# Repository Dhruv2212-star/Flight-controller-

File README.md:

# ASTRA FLIGHT CONTROLLER
The Astra Flight Controller is a custom-designed flight control board developed for multirotor unmanned aerial vehicles (UAVs). It is built around the STM32F411CEU6 microcontroller and the ICM-42688-P six-axis Inertial Measurement Unit (IMU), providing a compact, high-performance platform capable of running modern flight control firmware such as Betaflight, INAV, or customdeveloped firmware
1. **Main Features**
* STM32F411CEU6 ARM Cortex-M4 Microcontroller  
* ICM-42688-P 6-axis IMU  
* MP2359DJ High-Efficiency 5 V Buck Converter  
* AP2112K 3.3 V Low-Dropout Voltage Regulator  
* USB Type-C Interface  
* SWD Programming Header  
* XT30 Battery Input  
* Active Buzzer Driver Circuit  
* Status LED  
* External UART Expansion  
* Dedicated SPI Interface for the IMU  
* Compact PCB designed within a 100 mm × 100 mm manufacturing limit
  2. **Hardware Architecture**  
* Power Management  
* Processing Unit  
* Sensor System  
* Communication Interfaces  
* User Interface  
* Programming & Debugging  
* External Connections  
 3. **Hardware Modules Power Management**
Responsible for converting battery voltage into stable regulated voltages used by the board.
Major Components:
* XT30 Battery Connector  
* Resettable Fuse  
* MP2359DJ Buck Converter  
* AP2112K 3.3V Regulator Filtering Capacitors Outputs:  
 +5V Rail  
 +3.3V Rail  
4. **Processing Module**
The processing module is the "brain" of the flight controller. Main Component: STM32F411CEU6.
Responsibilities:  
* Reads sensor data  
* Executes flight control algorithms  
* Controls motors  
* Handles USB communication  
* Processes receiver input  
* Generates PWM/DShot signals    
* Controls LEDs and buzzer  
 5. **Sensor Module** 
The sensor subsystem provides real-time motion data.  
Main Sensor: ICM-42688-P.  
 
Measurements: 3-axis Accelerometer, 3-axis Gyroscope. Communication: SPI Interface.  
The IMU continuously measures angular velocity and acceleration  
**Power-Up Sequence**
*When battery power is applied, the following sequence occurs:*
Step 1: Battery voltage enters through the XT30 connector.  
Step 2: The resettable fuse protects the board from excessive current.  
Step 3: The MP2359DJ converts battery voltage into a regulated +5V supply.  
Step 4: The AP2112K converts +5V into +3.3V.  
Step 5: The STM32F411CEU6 receives stable power.   
Step 6: The crystal oscillator starts generating the system clock.  
Step 7: The microcontroller boots from Flash memory.  
Step 8: The SPI interface initializes the ICM-42688-P.  
Step 9: Sensors begin transmitting motion data.  
Step 10: the flight controller enters normal operating mode 

------------------------------------------------------------------------------------------------------------------------------------------

**Clock Generation**
The STM32F411CEU6 uses an external crystal oscillator for accurate timing. The external crystal provides stable CPU clock, accurate USB timing, reliable SPI communication, and consistent sensor sampling. Proper placement of the crystal and its load capacitors is essential for reliable operation.  

**power system**
Why Two Regulators?  
Using a single linear regulator directly from the battery would result in excessive heat generation, especially at higher input voltages. Instead, the Astra Flight Controller uses a two-stage regulation    
approach:  
* MP2359DJ Buck Converter — efficiently reduces battery voltage to 5 V.  
* AP2112K LDO — produces a clean and stable 3.3 V output with minimal electrical  
noise. This combination provides both efficiency and stable operation.  

**STM32F411CEU6 Microcontroller**
The STM32F411CEU6 is the primary processing unit of the Astra Flight Controller. It executes the flight control firmware, processes sensor data, generates motor outputs, and manages all communication interfaces.
Role-   
The STM32 reads IMU data through SPI, executes flight control algorithms, generates ESC outputs, monitors battery voltage, controls the LED and buzzer, manages USB communication, and supports firmware programming through SWD.  

## ICM-42688-P Inertial Measurement Unit (IMU)  
 *Introduction*  
The ICM-42688-P is the primary motion sensing device used in the Astra Flight Controller. It integrates a 3-axis accelerometer and a 3-axis gyroscope in a compact LGA package. The sensor continuously measures aircraft motion and sends this data to the STM32F411CEU6 through the SPI interface for attitude estimation and flight stabilization.    
**Why the ICM-42688-P was Selected?**  
The sensor was selected because of its excellent gyroscope noise performance, high sampling rate, low latency, low power consumption, compact size, and broad support in modern flight-control firmware such as Betaflight and INAV.  
Main Specifications:-  
* Device- ICM-42688-P  
* Sensor Type- 6-Axis IMU  
* Accelerometer- 3-Axis MEMS  
* Gyroscope- 3-Axis MEMS  
* Operating Voltage- 1.71–3.6 V  
* Communication- SPI / I²C  
* Max SPI Clock Up to 24 MHz  
* Operating Temp −40°C to +85°C    
**Working Principle**  
The accelerometer measures linear acceleration along the X, Y, and Z axes, while the gyroscope  
measures angular velocity about the same axes. Together they provide six degrees of freedom (6-DoF), allowing the firmware to estimate   the aircraft's orientation using sensor-fusion algorithms.  
**Hardware Integration**  
The IMU operates from the regulated 3.3 V rail. VDD and VDDIO are connected to 3.3 V, while the GND pins connect directly to the ground plane. Local decoupling capacitors are placed close to the power pins to reduce supply noise and improve stability.    
**SPI Communication**  
Communication with the STM32F411CEU6 takes place over SPI using SCK, MOSI, MISO, and CS. SPI was selected instead of I²C because it offers higher bandwidth, lower latency, and improved reliability in electrically noisy environments.  
**Interrupt Output**
The interrupt pin notifies the STM32 whenever new sensor data is available, reducing processor workload and improving the timing of the flight-control loop.  

The IMU continuously measures aircraft motion, sends accelerometer and gyroscope data to the STM32 through SPI, and the firmware processes this information to estimate attitude and generate motor control outputs.  

## USB Type-C Interface

*Introduction*  
The USB Type-C interface serves as one of the primary communication and power interfaces of the Astra Flight Controller. It provides firmware flashing, debugging, configuration, diagnostics and  
development power.  
USB Type-C offers reversible insertion, improved durability, better current capability and long-term compatibility. The design uses the USB 2.0 Full-Speed interface connected directly to the STM32F411CEU6.   

**Purpose**
Firmware upload, configuration using Betaflight/INAV/STM32CubeProgrammer, debugging through serial communication, and powering the board during development without a LiPo battery  
**Advantages**  
Reversible connector, stronger mechanical retention, higher current capability and modern industrystandard compatibility.  
**USB Connector**
| Pin | Function |  
| VBUS | +5V |  
| GND | Ground |  
| D+ | USB Data Positive |  
| D- | USB Data Negative |  
| CC1 | Configuration Channel 1 |  
| CC2 | Configuration Channel 2 |  
| Shield | Connector Shield |  

**Data Communication**
USB Full-Speed uses the D+ and D− differential pair. Route them together with matched lengths, minimal vias, constant spacing, no sharp bends and a continuous ground plane. The STM32F411CEU6 supports USB 2.0 Full-Speed (12 Mbps), sufficient for firmware updates and configuration  
##  XT30 Battery Connector
The XT30 connector is the primary battery input. Battery voltage enters the board through the XT30 connector, passes through the resettable fuse and protection circuitry, and then feeds the MP2359DJ buck converter. Wide copper traces are used to carry battery current and minimise voltage drop.  
## ESC Connections
Motor control signals generated by the STM32 are routed to the ESC outputs. These connections carry logiclevel control signals only; motor power is supplied separately by the battery through the ESCs.   
#  Indicators and User Interface
**Overview**  
The Astra Flight Controller includes a status LED, a TL3342 push button and an active buzzer. These devices provide visual, audible and manual interaction during development, testing and flight operation.  
**Status LED**
The STM32 controls the LED to indicate power, boot status, firmware activity, calibration, arming state and error conditions.  
**Push Button**
The TL3342 tactile switch can be used for boot mode selection, firmware recovery, calibration and user-defined functions through a GPIO input.  
**Active Buzzer**
The active buzzer provides audible feedback including startup, arming, low-battery and fault indications. It requires only an on/off control signal from the STM32.  
## Component Placement Strategy
1. Microcontroller Placement  
The STM32F411CEU6 is positioned near the center of the PCB. This location minimizes the average distance between the MCU and all connected peripherals, resulting in shorter SPI traces, shorter USB connections, reduced propagation delay, easier routing, and improved signal integrity. The exposed thermal pad beneath the MCU is connected directly to the ground plane for both thermal dissipation and electrical grounding.  
2. IMU Placement  
The ICM-42688-P is the most sensitive component on the board. To maximize Measurement accuracy, it is placed close to the center of the PCB, kept away from the MP2359DJ buck converter and inductor, and highcurrent traces are not routed beneath the sensor. A continuous ground plane is maintained underneath the device, and the sensor orientation matches the coordinate system  
expected by the firmware.  
Proper placement reduces electrical interference and vibration-induced measurement errors  
**Power Section Placement**
The power conversion circuitry is grouped together near the battery input. This includes:  
* XT30 connector.  
* Resettable fuse.  
* Protection diode.  
* MP2359DJ buck converter.  
* 4.7 µH Bourns SRP5030TA-4R7M inductor.  
* Input and output capacitors.  
* AP2112K voltage regulator.  
## Power Supply Design
The Astra Flight Controller is designed to operate directly from a 2S to 6S Lithium Polymer (LiPo) battery, meaning the input voltage can vary from approximately 7.4 V to 25.2 V. To achieve stable regulation, the Astra Flight Controller uses a two-stage power architecture: the MP2359DJ synchronous buck converter generates a regulated 5 V supply from the battery, and the AP2112K Low Dropout (LDO) regulator generates a clean 3.3 V supply from the 5 V raiL  

 Power Flow
2S–6S LiPo Battery  
|  
XT30 Battery Connector  
|  
Resettable Fuse (F1)  
|  
TVS / Reverse Protection  
|  
MP2359DJ Buck Converter — +5 V Rail  
|  
AP2112K LDO Regulator — +3.3 V Rail  
|  
STM32F411 
|  
ICM-42688  
##  Resettable Fuse (F1)
Immediately after the XT30 connector, the input passes through a resettable polyfuse (PTC), which protects the PCB from excessive current caused by short circuits, incorrect wiring, component failures, or assembly mistakes. Unlike a traditional fuse, the polyfuse automatically resets after the fault is removed and the device cools down.  

## MP2359DJ Buck Converter
1. Why a Buck Converter?
A linear regulator would dissipate the voltage difference between the battery and the output as heat. Converting 25.2 V from a fully charged 6S battery directly to 5 V using a linear regulator would result in excessive power loss and unacceptable temperatures. A switching buck converter solves this problem by rapidly switching the input voltage through an inductor and filtering the output,
achieving efficiencies typically above 85–90%.  
2. MP2359DJ Features  
* Wide input voltage range.  
* High conversion efficiency.  
* Integrated MOSFETs.  
* Compact package.  
* High switching frequency.  
* Internal protection features.  
* Minimal external components.  
3. Operating Principle  
The MP2359DJ is a synchronous step-down (buck) switching regulator. Its operation consists of four basic stages: the internal MOSFET switches ON allowing current to flow into the inductor; energy is stored in the magnetic field of the inductor; the MOSFET switches OFF; and the inductor releases stored energy through the output filter, maintaining a continuous output voltage. This cycle repeats
hundreds of thousands of times per second.
External Components-- 
● Input capacitor.
● Output capacitor.
● Bootstrap capacitor.
● Schottky protection diode (where applicable).
● Feedback resistor network.
● 4.7 µH power inductor

 # Manufacturing 
The PCB is designed to be compatible with standard manufacturing services such as JLCPCB while
remaining within the 100 mm × 100 mm board size 

# Screenshots
*Schematic*

*PCB tracing* 

*3D view*

 * Note-- the firmware needs to be programed according to the use, hence cannot be pre-programed

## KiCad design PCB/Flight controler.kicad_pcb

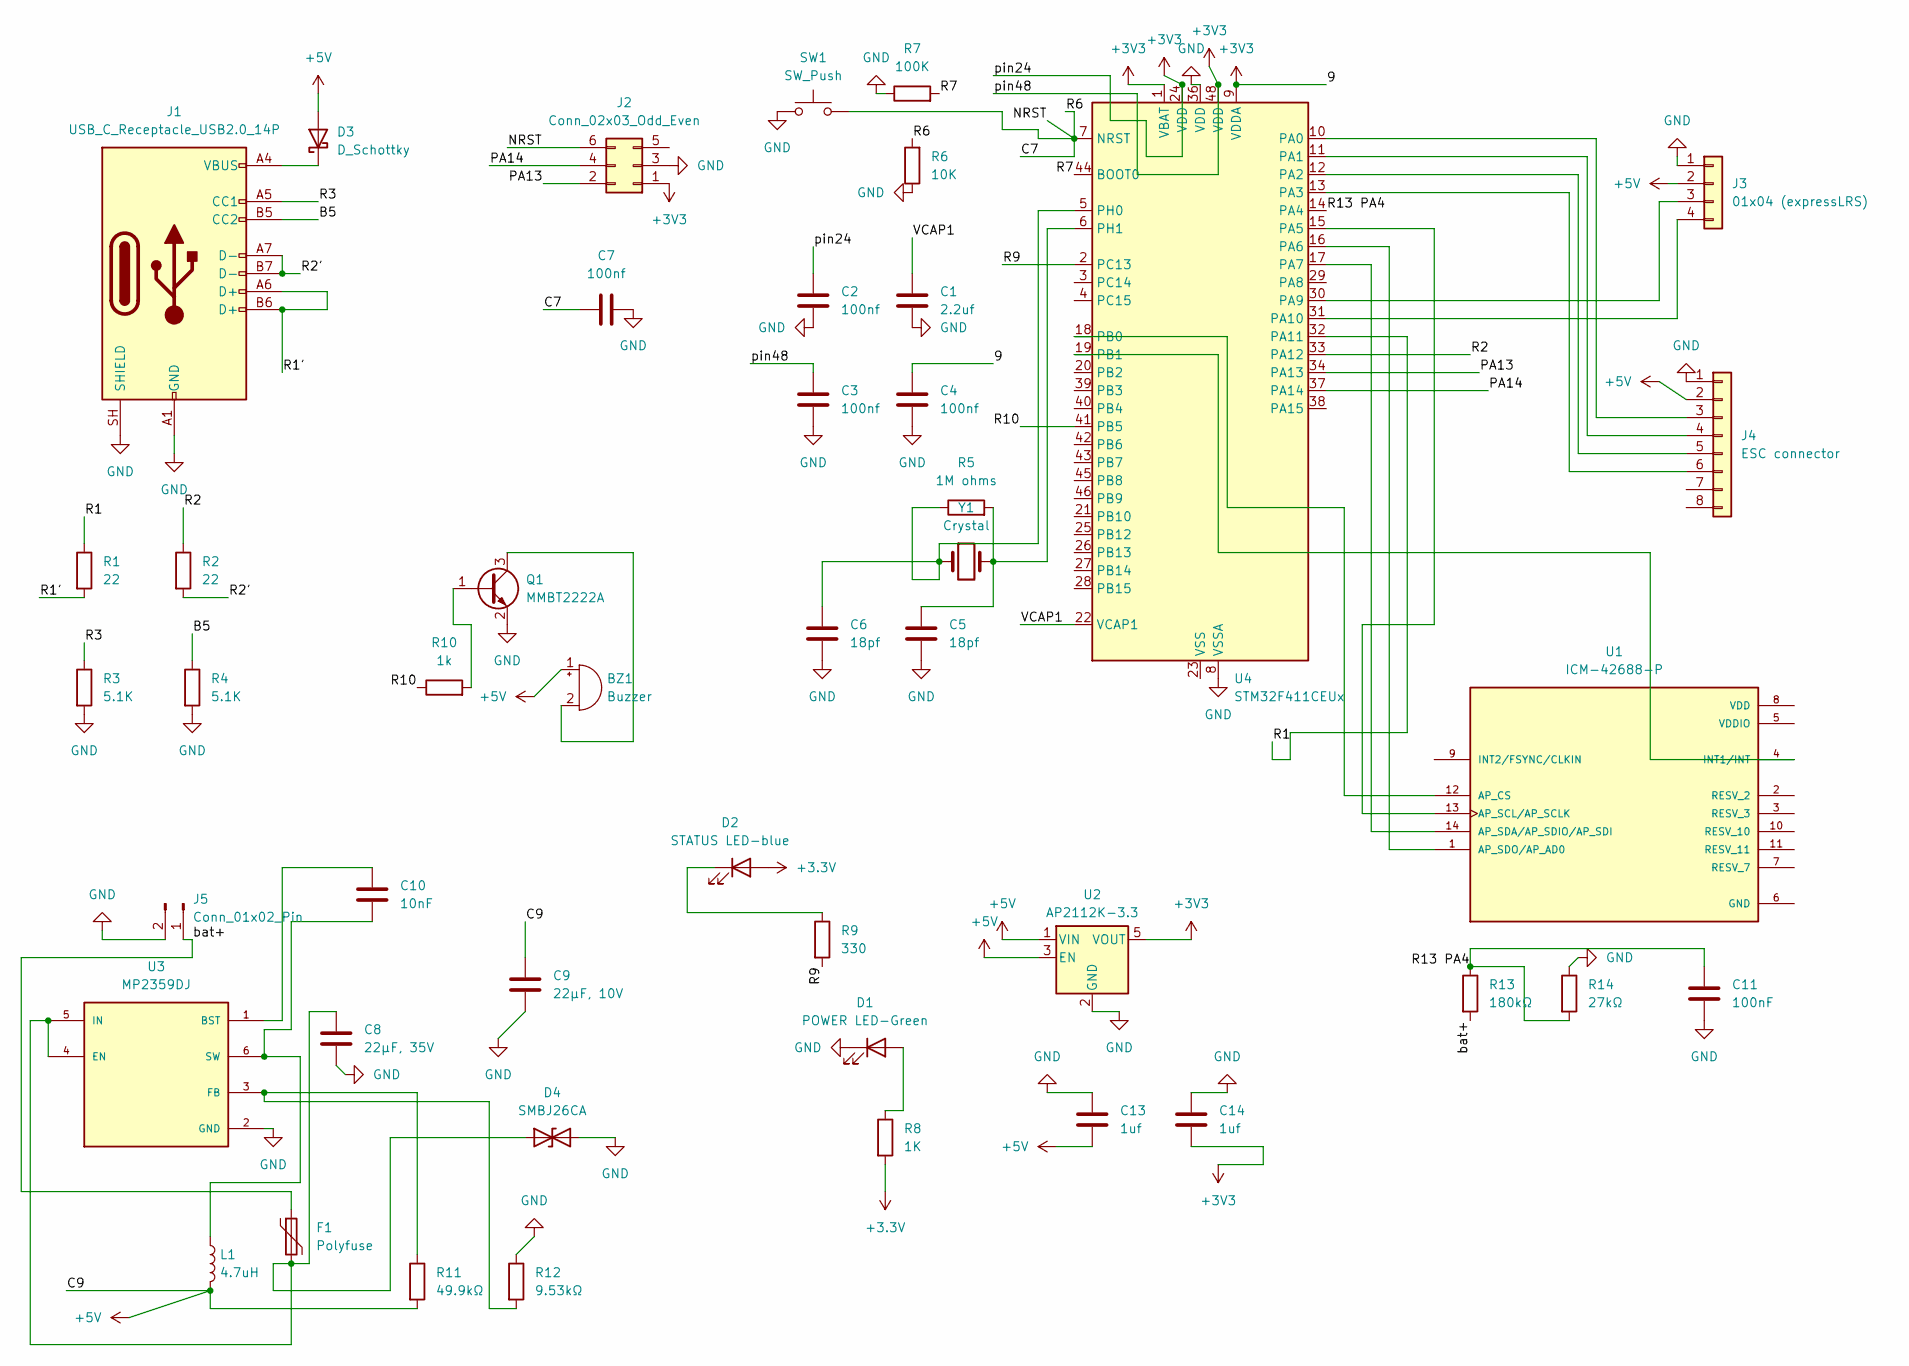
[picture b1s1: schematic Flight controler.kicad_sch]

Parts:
BZ1: Buzzer; Buzzer_12x9.5RM7.6
C1: 2.2uf; C_0603_1608Metric
C2, C3, C4, C7: 100nf; C_0603_1608Metric
C5, C6: 18pf; C_0603_1608Metric
C8: 22µF, 35V; C_1206_3216Metric
C9: 22µF, 10V; C_1206_3216Metric
C10: 10nF; C_0603_1608Metric
C11: 100nF; C_0603_1608Metric
C13, C14: 1uf; C_0603_1608Metric
D1: POWER LED-Green; LED_0603_1608Metric
D2: STATUS LED-blue; LED_0603_1608Metric
D3: D_Schottky; D_SMA
D4: SMBJ26CA; D_SMB
F1: Polyfuse; Fuse_1812_4532Metric
J1: USB_C_Receptacle_USB2.0_14P; USB_C_Receptacle_HRO_TYPE-C-31-M-12
J2: Conn_02x03_Odd_Even; PinHeader_2x03_P2.54mm_Vertical
J3: 01x04 (expressLRS); PinHeader_1x04_P2.54mm_Vertical
J4: ESC connector; PinHeader_1x08_P2.54mm_Vertical
J5: Conn_01x02_Pin; PinHeader_1x02_P2.54mm_Vertical
L1: 4.7uH; L_6.3x6.3_H3
Q1: MMBT2222A; TSOT-23-6
R1, R2: 22; R_0603_1608Metric
R3, R4: 5.1K; R_0603_1608Metric
R5: 1M ohms; R_0603_1608Metric
R6: 10K; R_0603_1608Metric
R7: 100K; R_0603_1608Metric
R8: 1K; R_0603_1608Metric
R9: 330; R_0603_1608Metric
R10: 1k; R_0603_1608Metric
R11: 49.9kΩ; R_0603_1608Metric
R12: 9.53kΩ; R_0603_1608Metric
R13: 180kΩ; R_0603_1608Metric
R14: 27kΩ; R_0603_1608Metric
SW1: SW_Push; SW_SPST_TL3342
U1: ICM-42688-P; PQFN50P300X250X97-14N; PARTREV 1.2
U2: AP2112K-3.3; SOT-23-5
U3: MP2359DJ; TSOT-23-6; PARTREV 1.21
U4: STM32F411CEUx; QFN-48-1EP_7x7mm_P0.5mm_EP5.6x5.6mm
Y1: Crystal; Crystal_SMD_3225-4Pin_3.2x2.5mm

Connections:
+3.3V: D2.2 (A), R8.2
+3V3: C2.1, C3.1, C4.1, C14.2, J2.1, U2.5 (VOUT), U4.1 (VBAT), U4.9 (VDDA), U4.24 (VDD), U4.48 (VDD)
+5V: BZ1.1 (+), C9.1, C13.2, D3.2 (A), J3.2, J4.2, L1.2, R11.2, U2.1 (VIN), U2.3 (EN)
/B5: J1.B5 (CC2), R4.1
/C7: C7.1, J2.6, R6.2, SW1.2, U4.7 (NRST)
/PA13: J2.2, U4.34 (PA13)
/PA14: J2.4, U4.37 (PA14)
/R1: R1.1, U4.32 (PA11)
/R1': J1.A6 (D+), J1.B6 (D+), R1.2
/R2: R2.1, U4.33 (PA12)
/R2': J1.A7 (D-), J1.B7 (D-), R2.2
/R3: J1.A5 (CC1), R3.1
/R7: R7.2, U4.44 (BOOT0)
/R9: R9.2, U4.2 (PC13)
/R10: R10.1, U4.41 (PB5)
/R13 PA4: C11.1, R13.1, R14.2, U4.14 (PA4)
/VCAP1: C1.1, U4.22 (VCAP1)
/bat+: F1.1, J5.1, R13.2
GND: C1.2, C2.2, C3.2, C4.2, C5.2, C6.2, C7.2, C8.2, C9.2, C11.2, C13.1, C14.1, D1.1 (K), D4.2 (A2), J1.A1 (GND), J1.A12 (GND), J1.B1 (GND), J1.B12 (GND), J1.SH (SHIELD), J2.3, J3.1, J4.1, J5.2, Q1.2 (E), R3.2, R4.2, R6.1, R7.1, R12.1, R14.1, SW1.1, U2.2 (GND), U3.2 (GND), U4.8 (VSSA), U4.36 (VDD)
unnamed: BZ1.2 (-), Q1.3 (C)
unnamed: D1.2 (A), R8.1
unnamed: D2.1 (K), R9.1
unnamed: D3.1 (K), J1.A4 (VBUS), J1.A9 (VBUS), J1.B4 (VBUS), J1.B9 (VBUS)
unnamed: C8.1, D4.1 (A1), F1.2, U3.4 (EN), U3.5 (IN)
unnamed: J3.3, U4.30 (PA9)
unnamed: J3.4, U4.31 (PA10)
unnamed: J4.3, U4.10 (PA0)
unnamed: J4.4, U4.11 (PA1)
unnamed: J4.5, U4.12 (PA2)
unnamed: J4.6, U4.13 (PA3)
unnamed: Q1.1 (B), R10.2
unnamed: U1.12 (AP_CS), U4.18 (PB0)
unnamed: U1.13 (AP_SCL/AP_SCLK), U4.15 (PA5)
unnamed: U1.14 (AP_SDA/AP_SDIO/AP_SDI), U4.17 (PA7)
unnamed: U1.1 (AP_SDO/AP_AD0), U4.16 (PA6)
unnamed: U1.4 (INT1/INT), U4.19 (PB1)
unnamed: C10.1, U3.1 (BST)
unnamed: R11.1, R12.2, U3.3 (FB)
unnamed: C10.2, L1.1, U3.6 (SW)
unnamed: C6.1, R5.1, U4.5 (PH0), Y1.1
unnamed: C5.1, R5.2, U4.6 (PH1), Y1.2
unnamed: U4.23 (VSS), U4.35 (VSS), U4.47 (VSS), U4.49 (VSS)

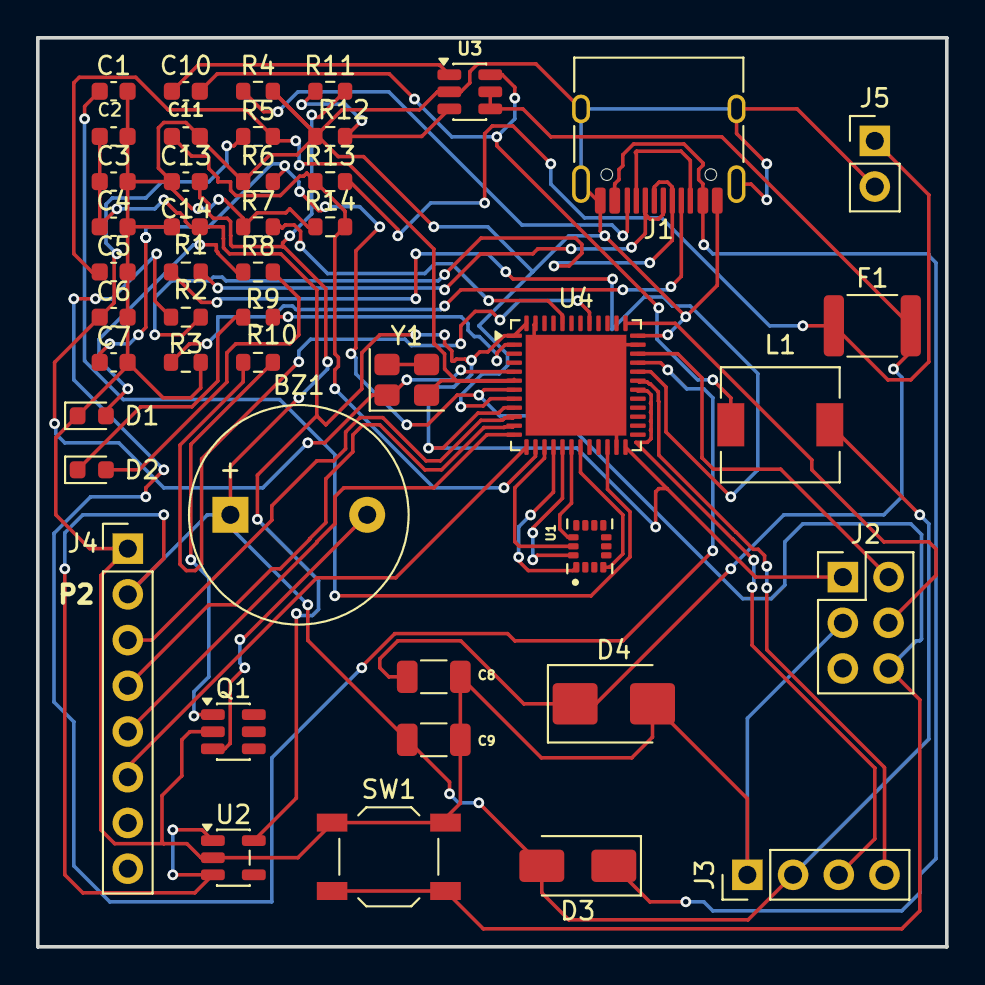
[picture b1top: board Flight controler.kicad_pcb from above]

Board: 2 copper layers, 50.5 x 50.5 mm, 46 parts (0 on the bottom side), 42 nets.

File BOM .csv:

Reference,Qty,Value
BZ1,1,Buzzer
C1,1,2.2uf
"C2,C3,C4,C7",4,100nf
"C5,C6",2,18pf
C8,1,"22µF, 35V"
C9,1,"22µF, 10V"
C10,1,10nF
C11,1,100nF
"C13,C14",2,1uf
D1,1,POWER LED-Green
D2,1,STATUS LED-blue
D3,1,D_Schottky
D4,1,SMBJ26CA
F1,1,Polyfuse
J1,1,USB_C_Receptacle_USB2.0_14P
J2,1,Conn_02x03_Odd_Even
J3,1,01x04 (expressLRS)
J4,1,ESC connector
J5,1,Conn_01x02_Pin
L1,1,4.7uH
Q1,1,MMBT2222A
"R1,R2",2,22
"R3,R4",2,5.1K
R5,1,1M ohms
R6,1,10K
R7,1,100K
R8,1,1K
R9,1,330
R10,1,1k
R11,1,49.9kΩ
R12,1,9.53kΩ
R13,1,180kΩ
R14,1,27kΩ
SW1,1,SW_Push
U1,1,ICM-42688-P
U2,1,AP2112K-3.3
U3,1,MP2359DJ
U4,1,STM32F411CEUx
Y1,1,Crystal
